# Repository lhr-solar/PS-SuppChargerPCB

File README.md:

# PS-SuppChargerPCB
Interfaces with supplemental battery to read BMS data and enable charging via USB-C or main battery pack

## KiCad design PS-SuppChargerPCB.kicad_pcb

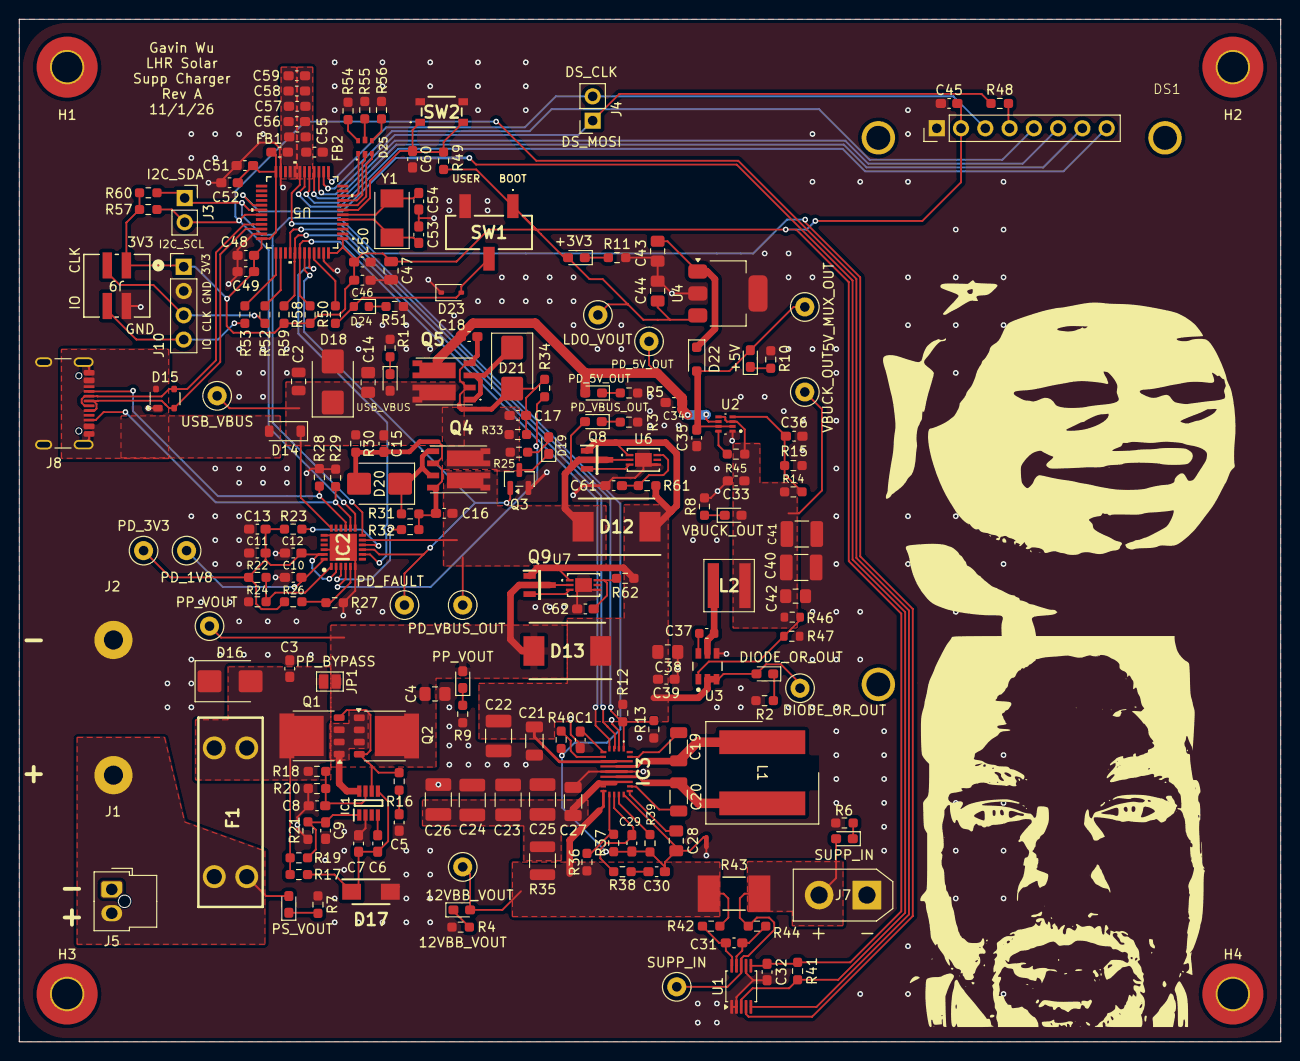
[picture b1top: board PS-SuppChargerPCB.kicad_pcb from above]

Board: 2 copper layers, 132.0 x 107.0 mm, 203 parts (0 on the bottom side), 106 nets.

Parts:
C1: 7.5n; C_0603_1608Metric_Pad1.08x0.95mm_HandSolder
C2: 10u; C_0805_2012Metric
C3, C8, C9, C31, C32, C33, C34, C35, C36, C45, C61, C62: 0.1u; C_0603_1608Metric_Pad1.08x0.95mm_HandSolder
C4, C43, C44: 10u; C_0805_2012Metric_Pad1.18x1.45mm_HandSolder
C5: 10n; C_0603_1608Metric_Pad1.08x0.95mm_HandSolder
C6: 220n; C_0603_1608Metric_Pad1.08x0.95mm_HandSolder
C7: 1u; C_0603_1608Metric_Pad1.08x0.95mm_HandSolder
C10, C11, C15, C16, C17, C18, C58, C59: 1uF; C_0603_1608Metric_Pad1.08x0.95mm_HandSolder
C12, C13, C46, C48, C49, C50, C51, C52, C56, C57, C60: 0.1uF; C_0603_1608Metric_Pad1.08x0.95mm_HandSolder
C14: 10uF; C_0805_2012Metric_Pad1.18x1.45mm_HandSolder
C19, C20, C21, C27: 0.1u; C_1206_3216Metric
C22, C23, C24, C25, C26, C40, C41: 22u; C_1210_3225Metric_Pad1.33x2.70mm_HandSolder
C28, C38: 4.7u; C_0805_2012Metric_Pad1.18x1.45mm_HandSolder
C29: 45p; C_0603_1608Metric_Pad1.08x0.95mm_HandSolder
C30: 90n; C_0603_1608Metric_Pad1.08x0.95mm_HandSolder
C37: 100n; C_0603_1608Metric
C39: 100n; C_0603_1608Metric_Pad1.08x0.95mm_HandSolder
C42: 3.3u; C_0805_2012Metric_Pad1.18x1.45mm_HandSolder
C47: 10uF; C_0805_2012Metric
C53, C54: 26p; C_0603_1608Metric_Pad1.08x0.95mm_HandSolder
C55: 100nF; C_0603_1608Metric_Pad1.08x0.95mm_HandSolder
D1: USB_VBUS; LED_0603_1608Metric_Pad1.05x0.95mm_HandSolder
D2: DIODE_OR_OUT; LED_0603_1608Metric_Pad1.05x0.95mm_HandSolder
D3: PD_VBUS_OUT; LED_0603_1608Metric_Pad1.05x0.95mm_HandSolder
D4: 12VBB_VOUT; LED_0603_1608Metric_Pad1.05x0.95mm_HandSolder
D5: PD_5V_OUT; LED_0603_1608Metric_Pad1.05x0.95mm_HandSolder
D6: SUPP_IN; LED_0603_1608Metric_Pad1.05x0.95mm_HandSolder
D7: PS_VOUT; LED_0603_1608Metric_Pad1.05x0.95mm_HandSolder
D8: VBUCK_OUT; LED_0603_1608Metric_Pad1.05x0.95mm_HandSolder
D9: PP_VOUT; LED_0603_1608Metric_Pad1.05x0.95mm_HandSolder
D10: +5V; LED_0603_1608Metric_Pad1.05x0.95mm_HandSolder
D11: +3V3; LED_0603_1608Metric_Pad1.05x0.95mm_HandSolder
D12, D13: B540C-13-F
D14: D_Schottky; D_SOD-123
D15: SP0503BAHT; SOT-143
D16: SMBJ15CA; D_SMB
D17: SMAF4758A; SODFL5026X125N
D18: SMBJ24A-E3_52; D_SMB
D19: FAULT; LED_0603_1608Metric_Pad1.05x0.95mm_HandSolder
D20, D21: SMBJ10A-E3_52; D_SMB
D22: SBA130CH-AU_R1_000A1; D_SOD-323_HandSoldering
D23: TVS; D_SOD-323
D24: LED; LED_0603_1608Metric
D25: RGB_LED
DS1: ZJY200S0800TG01
F1: Fuse_3557_2; Fuse-3557-2
FB1, FB2: FerriteBead; C_0603_1608Metric_Pad1.08x0.95mm_HandSolder
H1, H2, H3, H4: MountingHole_Pad; MountingHole_3.2mm_M3_Pad_TopBottom
IC1: LM74502DDFR
IC2: CYPD3177-24LQXQ
IC3: TPS552872RYQR; TPS552892QWRYQRQ1
J1: PS_Banana_+; Banana_Jack_1_Pin_4mm
J2: PS_Banana_-; Banana_Jack_1_Pin_4mm
J3: TP_I2C; PinSocket_1x02_P2.54mm_Vertical
J4: TP_DS SPI; PinSocket_1x02_P2.54mm_Vertical
J5: CarLVPowerConnector; Molex_Nano-Fit_105309-xx02_1x02_P2.50mm_Vertical
J7: Supp_Conn_xT30; AMASS_XT30UPB-M_1x02_P5.0mm_Vertical
J8: USB_C_Receptacle_USB2.0_16P; USB_C_Receptacle_GCT_USB4105-xx-A_16P_TopMnt_Horizontal
J9: SWD_Header; SWD_Conn
J10: SWD; PinHeader_1x04_P2.54mm_Vertical
JP1: PP_SolderJumper_2_Open; SolderJumper-2_P1.3mm_Open_Pad1.0x1.5mm
L1: 4.7u; 74439369082
L2: 8.2u; XAL5050822MEC
NT1: NetTie_2; NetTie-2_SMD_Pad0.5mm
Q1, Q2: PSMN012-100YS; LFPAK56
Q3: IRLML0030; SOT-23
Q4, Q5: SI7997DP-T1-GE3
Q8, Q9: NMOS; SOT95P237X112-3N
R1, R2, R3, R4, R5, R6, R7, R8, R9, R10, R15, R23, R57, R60: 4.7k; R_0603_1608Metric_Pad0.98x0.95mm_HandSolder
R11, R24, R25, R32, R34, R51, R54, R55, R56: 1k; R_0603_1608Metric_Pad0.98x0.95mm_HandSolder
R12: 15k; R_0603_1608Metric_Pad0.98x0.95mm_HandSolder
R13: 2.2k; R_0603_1608Metric_Pad0.98x0.95mm_HandSolder
R14: 16k; R_0603_1608Metric_Pad0.98x0.95mm_HandSolder
R16: 33; R_0603_1608Metric_Pad0.98x0.95mm_HandSolder
R17, R30, R41, R45, R49, R50: 10k; R_0603_1608Metric_Pad0.98x0.95mm_HandSolder
R18, R19, R36, R58, R59: 100k; R_0603_1608Metric_Pad0.98x0.95mm_HandSolder
R20: 7.32k; R_0603_1608Metric_Pad0.98x0.95mm_HandSolder
R21: 15.8k; R_0603_1608Metric_Pad0.98x0.95mm_HandSolder
R22, R26, R27, R28, R29: 5.1k; R_0603_1608Metric_Pad0.98x0.95mm_HandSolder
R31, R33: 49.9k; R_0603_1608Metric_Pad0.98x0.95mm_HandSolder
R35: 12.5m; R_1210_3225Metric
R37: 11.1k; R_0603_1608Metric_Pad0.98x0.95mm_HandSolder
R38: 1.455k; R_0603_1608Metric_Pad0.98x0.95mm_HandSolder
R39: R_US; R_0603_1608Metric_Pad0.98x0.95mm_HandSolder
R40: 50k; R_0603_1608Metric_Pad0.98x0.95mm_HandSolder
R42, R44: 10; R_0603_1608Metric_Pad0.98x0.95mm_HandSolder
R43: 10m; PMR100HZPFU10L0
R46: 100k; R_0603_1608Metric
R47: 19.1k; R_0603_1608Metric
R48, R52, R53: 22; R_0603_1608Metric_Pad0.98x0.95mm_HandSolder
R61, R62: 100; R_0603_1608Metric_Pad0.98x0.95mm_HandSolder
SW1: SW_SPDT; BootSW
SW2: Reset; TL3365AF180QG
TP1: USB_VBUS; TestPoint_Loop_D1.80mm_Drill1.0mm_Beaded
TP2: PD_5V_OUT; TestPoint_Loop_D1.80mm_Drill1.0mm_Beaded
TP3: PD_VBUS_OUT; TestPoint_Loop_D1.80mm_Drill1.0mm_Beaded
TP4: PP_VOUT; TestPoint_Loop_D1.80mm_Drill1.0mm_Beaded
TP5: DIODE_OR_OUT; TestPoint_Loop_D1.80mm_Drill1.0mm_Beaded
TP6: 12VBB_VOUT; TestPoint_Loop_D1.80mm_Drill1.0mm_Beaded
TP7: SUPP_IN; TestPoint_Loop_D1.80mm_Drill1.0mm_Beaded
TP8: VBUCK_OUT; TestPoint_Loop_D1.80mm_Drill1.0mm_Beaded
TP9: 5V_MUX_OUT; TestPoint_Loop_D1.80mm_Drill1.0mm_Beaded
TP10: LDO_VOUT; TestPoint_Loop_D1.80mm_Drill1.0mm_Beaded
TP12: PD_1V8; TestPoint_Loop_D1.80mm_Drill1.0mm_Beaded
TP13: PD_3V3; TestPoint_Loop_D1.80mm_Drill1.0mm_Beaded
TP14: PD_FAULT; TestPoint_Loop_D1.80mm_Drill1.0mm_Beaded
U1: INA226AIDGST; TSSOP-10_3x3mm_P0.5mm
U2: TPS2117DRLR
U3: LMR51635YFDDCR; DDC0006A-MFG
U4: MCP1826S; SOT-223-3_TabPin2
U5: STM32G473CETx; 48PinMCU
U6, U7: LTC4357HDCB-TRMPBF; DFN-6_DCB_LIT
Y1: Crystal; Crystal_SMD_Abracon_ABM3-2Pin_5.0x3.2mm

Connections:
+3V3: C32.1, C44.2, C45.1, C46.1, C47.1, C48.1, C49.1, C50.1, C51.1, C52.1, D11.2 (A), DS1.2 (VCC), FB1.1, J9.1, J10.1, R41.1, R49.2, R57.1, R58.1, R59.1, R60.1, SW1.1 (A), TP10.1 (1_1), U1.6 (VS), U4.3 (VO), U5.1 (VBAT), U5.24 (VDD), U5.36 (VDD), U5.48 (VDD)
+5V: C35.1, D10.2 (A), D22.2 (A), TP9.1 (1_1), U2.2 (VOUT), U2.7 (VOUT__1)
+14.7V: D6.2 (A), J7.2, R43.2, R44.2, TP7.1 (1_1), U1.8 (Vbus)
+15V: C16.1, D3.2 (A), D12.2 (A), IC2.11 (VDC_OUT), Q4.5 (D2), Q4.6 (D2), Q4.10 (D2), Q4.12 (D2), Q8.3 (S), TP3.1 (1_1), U6.2 (IN)
/12VBB_CC: IC3.4 (~CC), R58.2, U5.42 (PB5)
/12VBB_PG: IC3.3 (PG), R59.2, U5.41 (PB4)
/12VBB_VOUT: D4.2 (A), IC3.13 (ISN), R35.2, R36.2, R42.2, R43.1, TP6.1 (1_1)
/12VBuck/CB: C37.1, U3.6 (CB)
/12VBuck/FB: R46.2, R47.1, U3.1 (FB)
/12VBuck/SW: C37.2, L2.1, U3.5 (SW)
/12VBuckBoost/DITH/SYNC: C1.1, IC3.5 (DITH/SYNC)
/CC1: IC2.15 (CC1), J8.A5 (CC1), R28.1
/CC2: IC2.14 (CC2), J8.B5 (CC2), R29.1
/CurrentVoltageSensing/Vin+: C31.1, R42.1, U1.10 (Vin+)
/CurrentVoltageSensing/Vin-: C31.2, R44.1, U1.9 (Vin-)
/DIODE_OR_OUT: C21.1, C22.1, C38.1, C39.1, D2.2 (A), D12.1 (K), D13.1 (K), IC3.7 (VIN), Q8.1 (D), Q9.1 (D), R12.1, R61.1, R62.1, TP5.1 (1_1), U3.2 (EN), U3.3 (VIN), U6.1 (OUT), U7.1 (OUT)
/DS_BLK: DS1.8 (BLK), U5.18 (PB2)
/DS_CLK: DS1.3 (SCL), J4.2, U5.13 (PA5)
/DS_CS: DS1.7 (CS), U5.17 (PB1)
/DS_DC: DS1.6 (DC), U5.16 (PB0)
/DS_MOSI: J4.1, R48.1, U5.15 (PA7)
/DS_RES: DS1.5 (RES), U5.14 (PA6)
/EN: IC3.1 (EN/UVLO), R12.2, R13.1, U5.40 (PB3)
/I2C_SCL: IC2.13 (HPI_SCL), J3.2, R57.2, U1.5 (SCL), U5.31 (PA9)
/I2C_SDA: IC2.12 (HPI_SDA), J3.1, R60.2, U1.4 (SDA), U5.30 (PA8)
/INA_ALERT: R41.2, U1.3 (~Alert), U5.29 (PB15)
/PD_5V_OUT: C18.1, C34.1, D5.2 (A), Q5.5 (D2), Q5.6 (D2), Q5.10 (D2), Q5.12 (D2), TP2.1 (1_1), U2.6 (VIN2)
/PD_FAULT: IC2.9 (FAULT), Q3.1 (G), TP14.1 (1_1), U5.43 (PB6)
/PD_GPIO_1: IC2.8 (GPIO_1), U5.44 (PB7)
/PP_VIN: C3.1, D16.2 (A2), F1.2, JP1.2 (B), Q1.5, R17.2, R18.1, R19.1
/PP_VOUT: C4.1, D9.2 (A), D13.2 (A), JP1.1 (A), Q2.5, Q9.3 (S), TP4.1 (1_1), U7.2 (IN)
/PS_VOUT: D7.2 (A), F1.1, J1.1 (Pin_1_1), J5.2 (+12V)
/Peripherals/48PinMCU/BOOT0: R50.1, U5.45 (PB8-BOOT0)
/Peripherals/48PinMCU/NRST: C60.1, R49.1, SW2.1, U5.7 (PG10-NRST)
/Peripherals/48PinMCU/PA0: D25.5, U5.8 (PA0-GPIO_BLUE)
/Peripherals/48PinMCU/PA1: D25.3, U5.9 (PA1_GPIO_RED)
/Peripherals/48PinMCU/PA2: D25.1, U5.10 (PA2-GPIO_GREEN)
/Peripherals/48PinMCU/SWCLK: R52.1, U5.38 (PA14)
/Peripherals/48PinMCU/SWDIO: R53.1, U5.37 (PA13)
/Peripherals/48PinMCU/VDDA: C55.1, C56.1, C57.1, C58.1, C59.1, FB1.2, U5.20 (VREF+), U5.21 (VDDA)
/PowerProtection/EN/UVLO: C9.1, IC1.1 (EN/UVLO), R19.2, R21.2
/PowerProtection/OV: C8.1, IC1.7 (OV), R18.2, R20.1
/PowerProtection/gate: IC1.6 (GATE), Q1.4, Q2.4, R16.2
/PowerProtection/source: IC1.8 (SRC), Q1.1, Q1.2, Q1.3, Q2.1, Q2.2, Q2.3
/Power_Mux/PR1: C36.1, R14.2, R15.1, U2.4 (PR1)
/USB-C_Connector/VBUS_IN: D14.2 (A), D15.4 (K), J8.A4 (VBUS), J8.A9 (VBUS), J8.B4 (VBUS), J8.B9 (VBUS)
/USB_D+: D15.2 (K), J8.A6 (D+), J8.B6 (D+), U5.34 (PA12)
/USB_D-: D15.3 (K), J8.A7 (D-), J8.B7 (D-), U5.33 (PA11)
/USB_PD/ISINK_COARSE: IC2.5 (ISNK_COARSE), R26.2, R27.1
/USB_PD/PD_1V8: C10.2, IC2.24 (VCCD), TP12.1 (1_1)
/USB_PD/PD_3V3: C11.1, C12.1, C13.1, IC2.2 (VBUS_MAX), IC2.23 (VDDD), R22.1, R23.1, R26.1, TP13.1 (1_1)
/USB_PD/SAFE_PWR_EN: IC2.4 (SAFE_PWR_EN), R34.2
/USB_PD/VBUS_FET_EN: IC2.3 (VBUS_FET_EN), R32.2
/USB_PD/VBUS_MIN: IC2.1 (VBUS_MIN), R22.2, R24.1
/USB_VBUS: C2.2, C14.1, C15.1, C17.1, D1.2 (A), D14.1 (K), D18.1 (K), IC2.18 (VBUS_IN), Q4.7 (D1), Q4.8 (D1), Q4.9 (D1), Q4.11 (D1), Q5.7 (D1), Q5.8 (D1), Q5.9 (D1), Q5.11 (D1), R25.1, R30.2, R33.2, TP1.1 (1_1)
/VBUCK_OUT: C33.1, C40.1, C41.1, C42.1, D8.2 (A), L2.2, R14.1, R45.1, R46.1, TP8.1 (1_1), U2.3 (VIN1), U2.5 (MODE)
GND: C1.2, C2.1, C3.2, C4.2, C5.2, C7.1, C8.2, C9.2, C10.1, C11.2, C12.2, C13.2, C14.2, C21.2, C22.2, C23.2, C24.2, C25.2, C26.2, C27.2, C32.2, C33.2, C34.2, C35.2, C36.2, C38.2, C39.2, C40.2, C41.2, C42.2, C43.1, C44.1, C45.2, C46.2, C47.2, C48.2, C49.2, C50.2, C51.2, C52.2, C53.1, C54.2, C60.2, C61.2, C62.2, D15.1 (A), D16.1 (A1), D17.2 (A), D18.2 (A), D23.1 (A1), DS1.1 (GND), FB2.2, IC1.2 (GND), IC2.6 (ISNK_FINE), IC2.19 (GND_1), IC2.22 (GND_2), IC2.25 (GND_3), IC3.2 (MODE), IC3.9 (PGND_1), IC3.22 (PGND_2), IC3.23 (PGND_3), J2.1 (Pin_1_1), J5.1 (GND), J7.1, J8.A1 (GND), J8.A12 (GND), J8.B1 (GND), J8.B12 (GND), J8.S1 (SHIELD), J8.S2 (Shield), J8.S3 (Shield), J8.S4 (Shield), J9.2, J10.2, NT1.1, Q3.2 (S), R1.2, R2.2, R3.2, R4.2, R5.2, R6.2, R7.2, R8.2, R9.2, R10.2, R11.2, R13.2, R15.2, R20.2, R21.1, R24.2, R27.2, R28.2, R29.2, R47.2, R51.2, R54.2, R55.2, R56.2, SW1.3 (C), SW2.2, U1.1 (A1), U1.2 (A0), U1.7 (GND), U2.1 (GND), U3.4 (GND), U4.2 (GND), U5.23 (VSS), U5.35 (VSS), U5.47 (VSS), U6.4 (GND), U6.7 (EPAD), U7.4 (GND), U7.7 (EPAD)
GNDA: C28.2, C29.2, C30.2, C55.2, C56.2, C57.2, C58.2, C59.2, FB2.1, IC3.17 (AGND), NT1.2, R37.2, R39.1, R40.1, U5.19 (VSSA)
unnamed: C5.1, R16.1
unnamed: C30.1, R38.2
unnamed: D1.1 (K), R1.1
unnamed: D2.1 (K), R2.1
unnamed: D3.1 (K), R3.1
unnamed: D4.1 (K), R4.1
unnamed: D5.1 (K), R5.1
unnamed: D6.1 (K), R6.1
unnamed: D7.1 (K), R7.1
unnamed: D8.1 (K), R8.1
unnamed: D9.1 (K), R9.1
unnamed: D10.1 (K), R10.1
unnamed: D11.1 (K), R11.1
unnamed: C6.1, C7.2, D17.1 (K), IC1.5 (VS), R17.1
unnamed: D19.2 (A), R25.2
unnamed: D19.1 (K), Q3.3 (D)
unnamed: C15.2, C16.2, D20.2 (A), Q4.2 (G1), Q4.4 (G2), R30.1, R31.1, R32.1
unnamed: D20.1 (K), Q4.1 (S1), Q4.3 (S2), R31.2
unnamed: C17.2, C18.2, D21.2 (A), Q5.2 (G1), Q5.4 (G2), R33.1, R34.1
unnamed: D21.1 (K), Q5.1 (S1), Q5.3 (S2)
unnamed: C43.2, D22.1 (K), U4.1 (VI)
unnamed: D23.2 (A2), D24.2 (A), R50.2, SW1.2 (B)
unnamed: D24.1 (K), R51.1
unnamed: D25.2, R54.1
unnamed: D25.4, R55.1
unnamed: D25.6, R56.1
unnamed: DS1.4 (SDA), R48.2
unnamed: C6.2, IC1.4 (VCAP)
unnamed: IC2.10 (FLIP), R23.2
unnamed: C19.2, IC3.20 (BOOT1)
unnamed: C20.2, IC3.19 (BOOT2)
unnamed: IC3.16 (CDC), R39.2
unnamed: C29.1, IC3.15 (COMP), R38.1
unnamed: IC3.14 (FB), R36.1, R37.1
unnamed: IC3.6 (FSW), R40.2
unnamed: C23.1, C24.1, C25.1, C26.1, C27.1, IC3.11 (VOUT), IC3.12 (ISP), R35.1
unnamed: C19.1, IC3.8 (SW1), L1.1
unnamed: C20.1, IC3.10 (SW2), L1.2
unnamed: C28.1, IC3.18 (VCC)
unnamed: J9.3, J10.3, R52.2
unnamed: J9.4, J10.4, R53.2
unnamed: Q8.2 (G), U6.3 (GATE)
unnamed: Q9.2 (G), U7.3 (GATE)
unnamed: R45.2, U2.8 (ST)
unnamed: C53.2, U5.5 (PF0-OSC_IN), Y1.1
unnamed: C54.1, U5.6 (PF1-OSC_OUT), Y1.2
unnamed: C61.1, R61.2, U6.6 (VDD)
unnamed: C62.1, R62.2, U7.6 (VDD)
